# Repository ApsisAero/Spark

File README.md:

# Spark

A static testing sensor array and ignition system designed to assist in the evaluation of solid fuel rocket engines.

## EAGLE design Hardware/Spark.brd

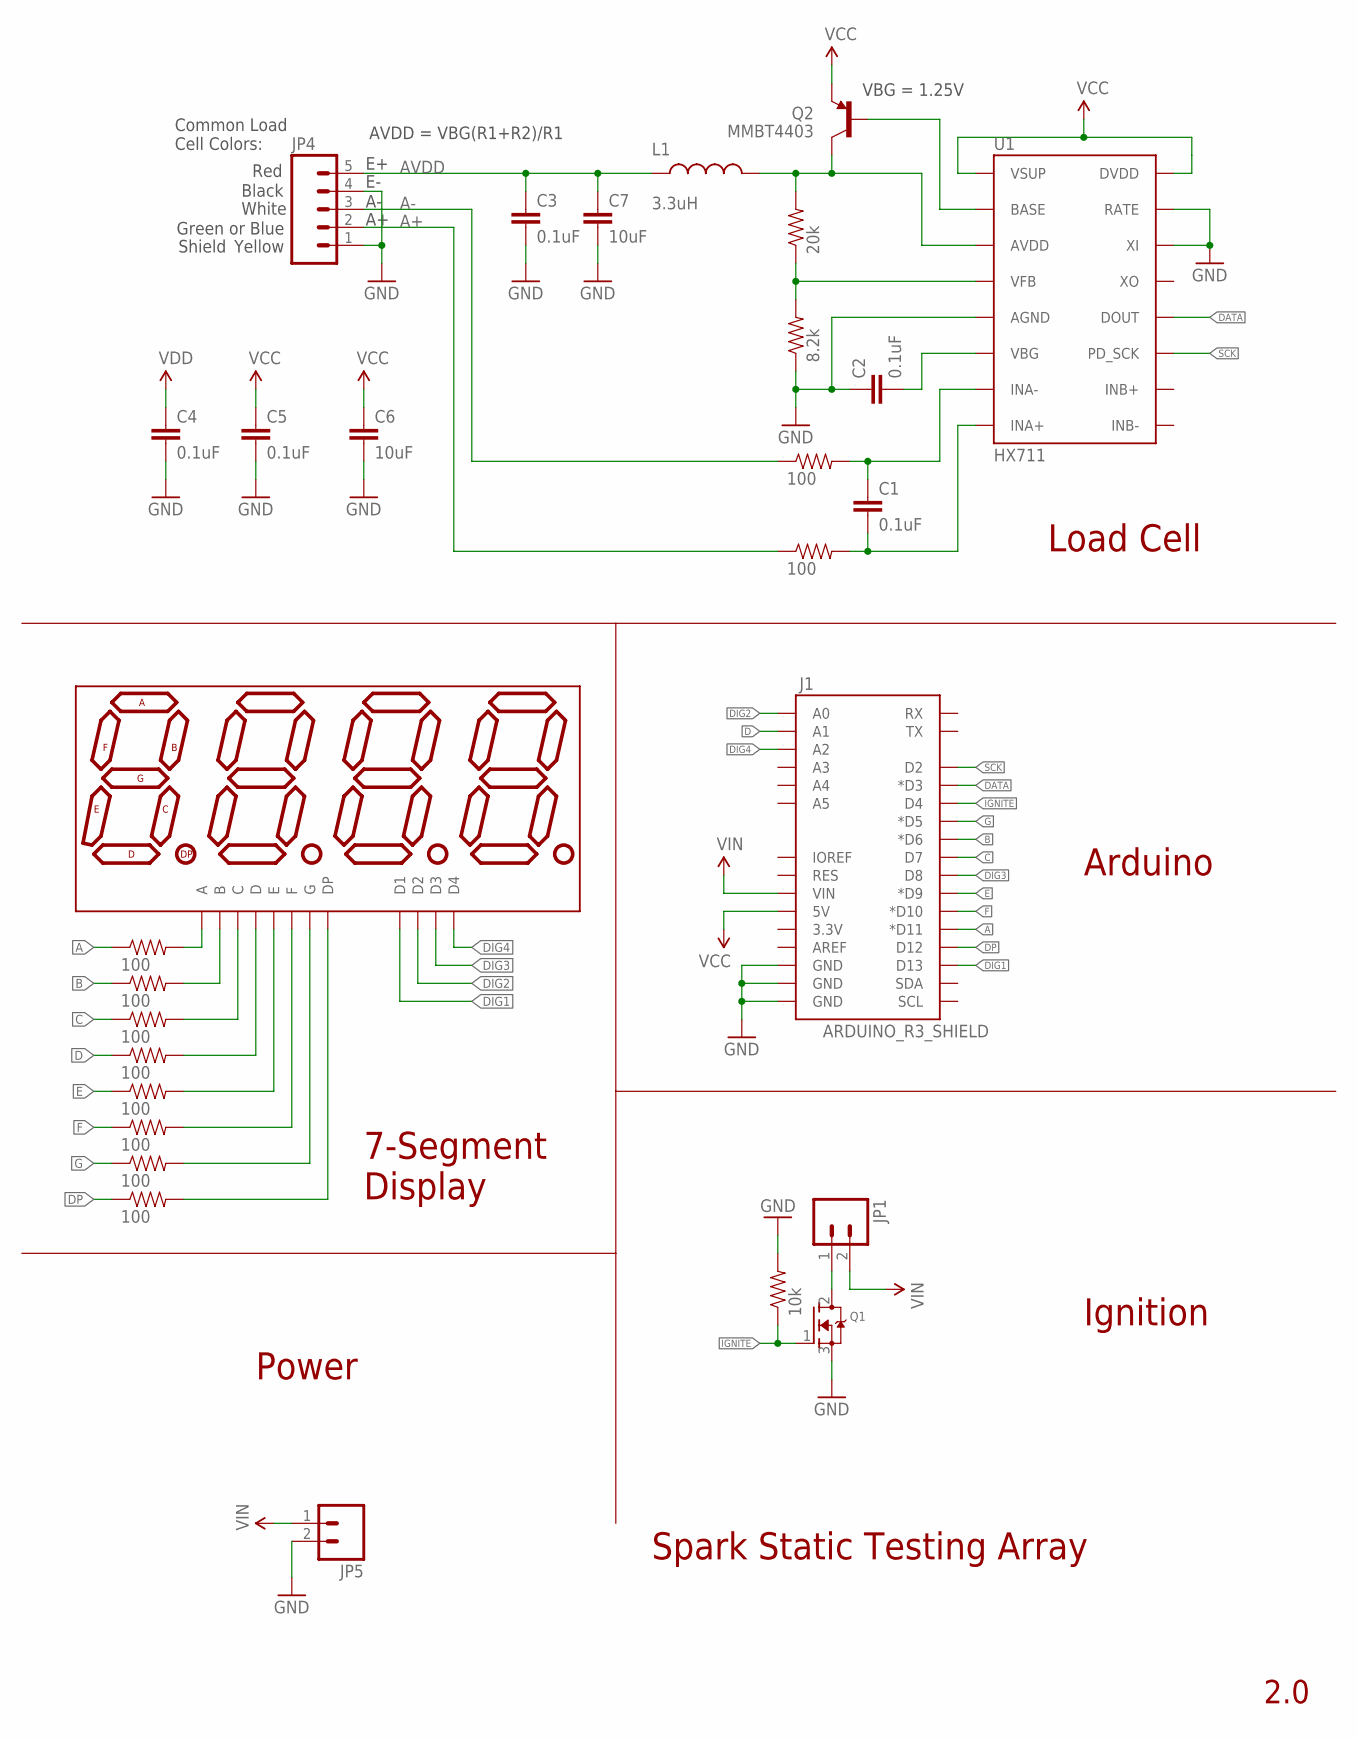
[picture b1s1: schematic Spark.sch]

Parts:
C1, C2, C3, C4, C5: 0.1uF; 0603-CAP
C6, C7: 10uF; 1210
J1: ARDUINO_R3_SHIELD; UNO_R3_SHIELD
JP1, JP5: M025MM; SCREWTERMINAL-5MM-2
JP4: M05PTH; 1X05
L1: 3.3uH; 0805
Q1: MOSFET-NGDS_TO220V; TO220V
Q2: MMBT4403; SOT23-3
R1: 10k; 0805
R3, R4, R6, R7, R8, R9, R10, R11, R12, R13: 100; 0805
R14: 8.2k; 0805
R15: 20k; 0805
U1: HX711; SO16
U$1: 7-SEGMENT-4DIGIT-COUNTERPTH; 7-SEGMENT-4DIGIT-COUNTER

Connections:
A: J1.D11 (*D11), R13.1
A+: JP4.2, R4.1
A-: JP4.3, R3.1
AVDD: C3.1, C7.1, JP4.5, L1.1
B: J1.D6 (*D6), R6.1
C: J1.D7, R7.1
D: J1.A1, R8.1
DATA: J1.D3 (*D3), U1.12 (DOUT)
DIG1: J1.D13, U$1.12 (D1)
DIG2: J1.A0, U$1.9 (D2)
DIG3: J1.D8, U$1.8 (D3)
DIG4: J1.A2, U$1.6 (D4)
DP: J1.D12, R12.1
E: J1.D9 (*D9), R9.1
F: J1.D10 (*D10), R10.1
G: J1.D5 (*D5), R11.1
GND: C2.1, C3.2, C4.2, C5.2, C6.2, C7.2, J1.GND@0 (GND), J1.GND@1 (GND), J1.GND@2 (GND), JP4.1, JP4.4, JP5.2, Q1.3 (S), R1.2, R14.1, U1.5 (AGND), U1.14 (XI), U1.15 (RATE)
IGNITE: J1.D4, Q1.1 (G), R1.1
unnamed: JP1.1, Q1.2 (D)
unnamed: C1.1, R3.2, U1.7 (INA-)
unnamed: Q2.1 (B), U1.2 (BASE)
unnamed: L1.2, Q2.3 (C), R15.2, U1.3 (AVDD)
unnamed: R14.2, R15.1, U1.4 (VFB)
unnamed: C2.2, U1.6 (VBG)
unnamed: C1.2, R4.2, U1.8 (INA+)
unnamed: R13.2, U$1.11 (A)
unnamed: R6.2, U$1.7 (B)
unnamed: R7.2, U$1.4 (C)
unnamed: R8.2, U$1.2 (D)
unnamed: R9.2, U$1.1 (E)
unnamed: R10.2, U$1.10 (F)
unnamed: R11.2, U$1.5 (G)
unnamed: R12.2, U$1.3 (DP)
SCK: J1.D2, U1.11 (PD_SCK)
VCC: C5.1, C6.1, J1.5V, Q2.2 (E), U1.1 (VSUP)
VDD: C4.1
VIN: J1.VIN, JP1.2, JP5.1

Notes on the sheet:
VBG = 1.25V
AVDD = VBG(R1+R2)/R1
Red
Black
White
Green or Blue
Common Load Cell Colors:
Shield
Yellow
Load Cell
Power
7-Segment Display
Arduino
Ignition
Spark Static Testing Array
2.0

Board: 2 copper layers, 29 parts (0 on the bottom side), 36 nets, no tracks yet.

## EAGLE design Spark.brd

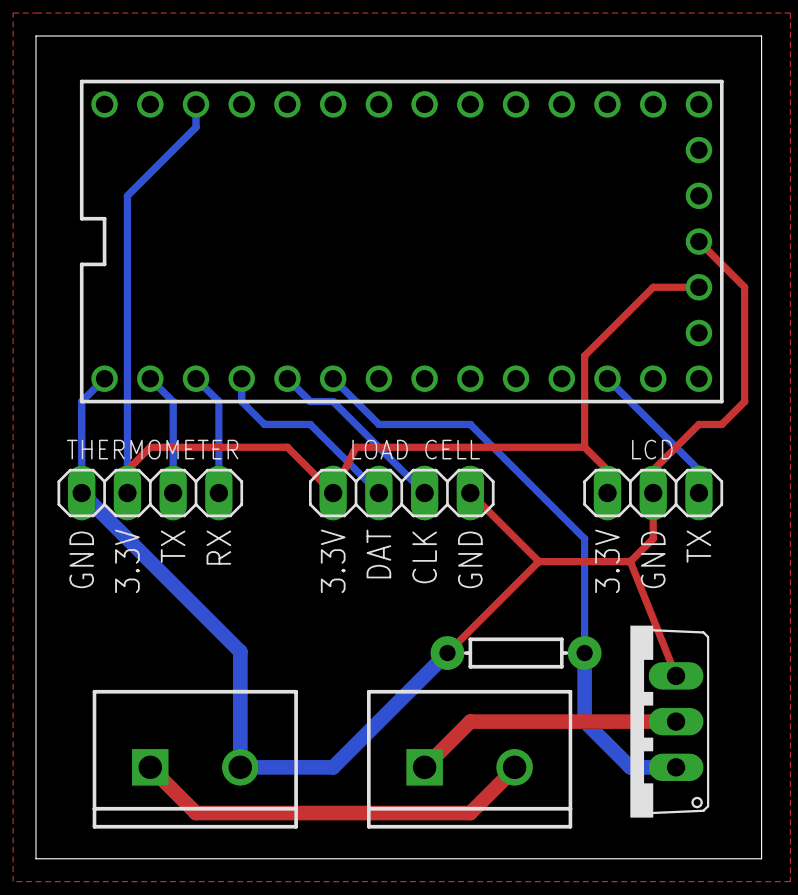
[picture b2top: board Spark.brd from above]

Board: 2 copper layers, 40.3 x 45.7 mm, 8 parts (0 on the bottom side), 10 nets.

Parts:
JP1, JP5: SCREWTERMINAL-5MM-2
JP2, JP3: 1X04
JP4: 1X03
Q1: TO220V
R1: AXIAL-0.3EZ
U$1: TEENSY_3.1_BASIC

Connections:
3.3V: JP2.3, JP3.1, JP4.1, U$1.3.3V, U$1.3.3V1
CLK: JP3.3, U$1.3
DAT: JP3.2, U$1.2
GND: JP2.4, JP3.4, JP4.2, JP5.2, Q1.3, R1.P$1, U$1.GND, U$1.GND1
IGNITE: Q1.1, R1.P$2, U$1.4
unnamed: JP1.1, Q1.2
RX: JP2.2, U$1.0
TX: JP2.1, U$1.1
TX2: JP4.3, U$1.10
VCC: JP1.2, JP5.1

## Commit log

2015-10-13 ignition circuit
2015-10-13 thermometer interface
2015-10-14 teensy
2015-10-14 initial board design
2015-10-14 ground fill and better silkscreen
2015-10-14 initial firmware
2015-10-14 mosfet and lcd debug
2015-10-17 organization and test functions
2015-10-18 initial live graphing from serial
2015-10-19 added axis labels
2015-10-28 new python code
2015-10-28 added arduino time
2015-10-28 python fixes and it works!
    ignition test succesful.
2015-10-28 initial spark case
2015-10-28 added ports and stuff
2015-10-28 csv output
    untested
2015-10-28 testing and zeroing
    confirmed to work
2015-10-29 fixes and organization
2015-10-29 ui and constants
2015-10-29 a pretty gui
    sparse but it works
    has same functionality as command line
2015-10-29 LCD code complete
    verbose only supported with GUI
2015-10-29 spark case 3dp files
2015-10-29 added 10ms delay
2015-10-30 added delay function
2015-12-02 load cell calib
2016-10-15 begin v2
2016-10-15 7-segment and arduino
2016-10-15 prettify v2 schematic
2016-10-15 ground arduino
2016-10-15 switch to 0805 packages
2016-10-15 begin layout

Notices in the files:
parts and their libraries:
SparkFun-Connectors: Licensing: Creative Commons ShareAlike 4.0 International - https://creativecommons.org/licenses/by-sa/4.0
SparkFun-Displays: Licensing: CC v3.0 Share-Alike You are welcome to use this library for commercial purposes.
